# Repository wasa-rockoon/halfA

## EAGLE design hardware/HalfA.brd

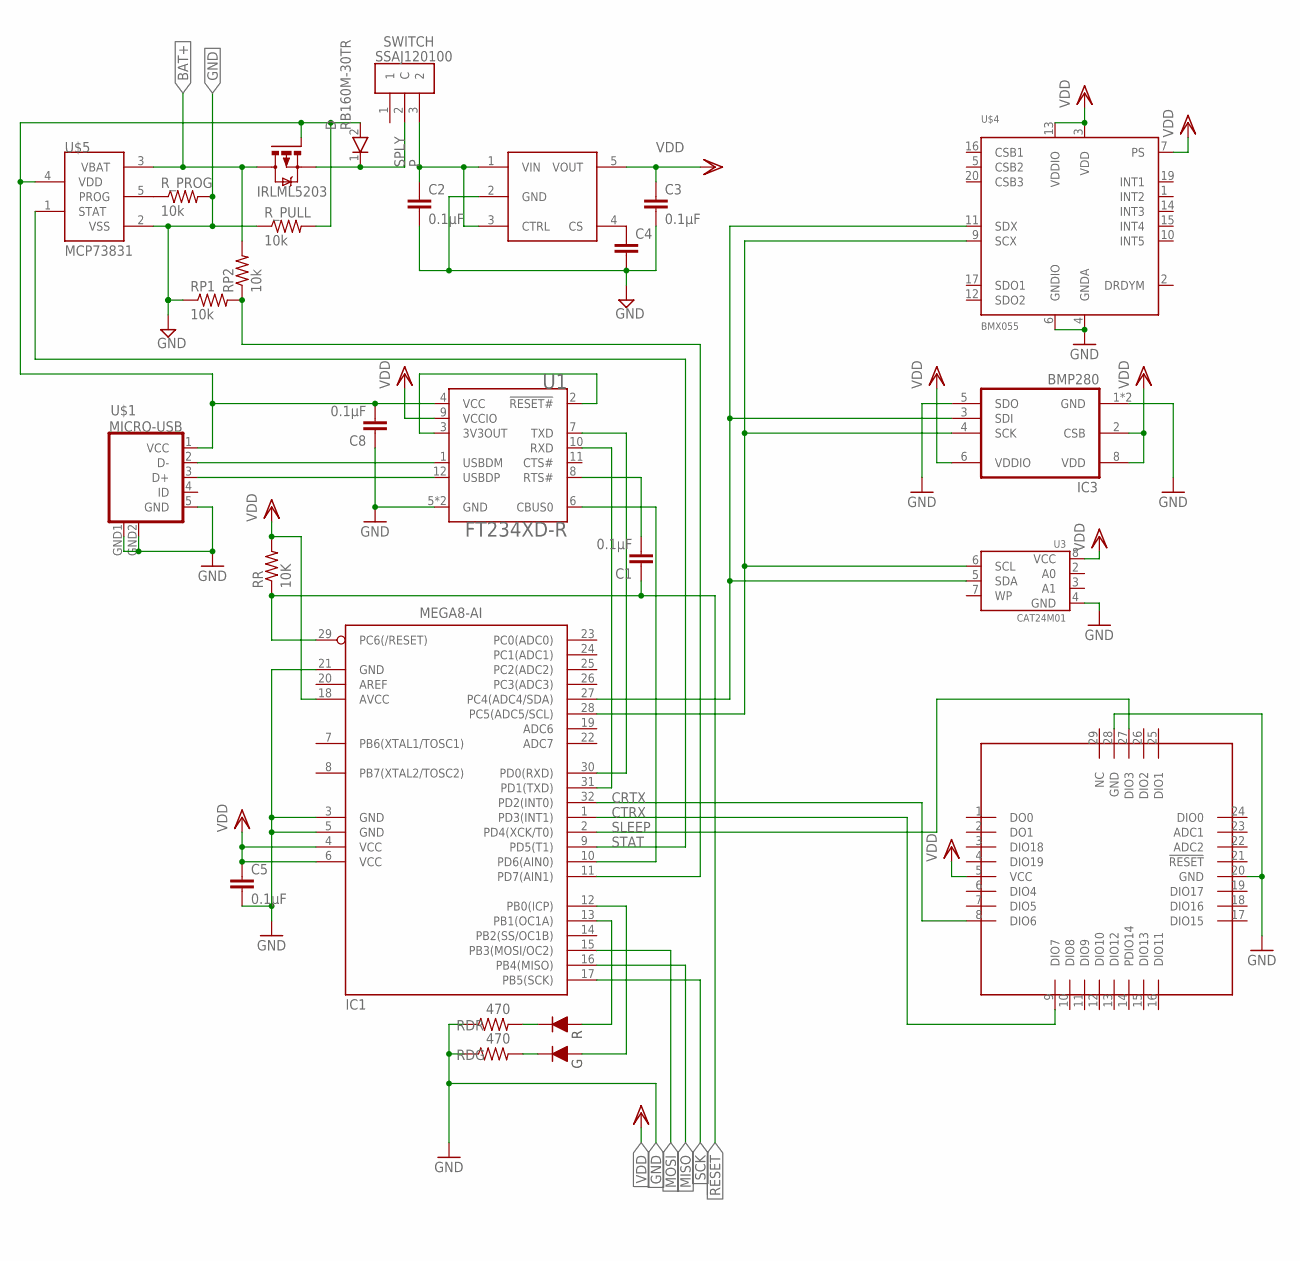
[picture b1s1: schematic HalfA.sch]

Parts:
C1, C2, C3, C5, C8: 0.1µF; C0402K
C4: C-EUC0402K; C0402K
D: RB160M-30TR; SODFL3516X90N
IC1: MEGA8-AI; TQFP32-08
IC3: BMP280
Q1: IRLML5203; MICRO3
RDG: 470; R0402
RDR: 470; R0402
RP1, RP2: 10k; R0402
RR: 10K; R0402
R_PROG: 10k; R0402
R_PULL: 10k; R0402
SWITCH: SSAJ120100
U1: FT234XD-R; SON45P300X300X80-13N
U3: CAT24M01; SO-8
U$1: MICRO-USB
U$2: NJM12888F
U$3: LITE
U$4: BMX055
U$5: MCP73831; SOT23-5L
U$6: SML-P24MUW

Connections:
3.3V: U1.2 (!RESET#), U1.3 (3V3OUT)
5V: C8.2, D.2 (A), Q1.1 (G), R_PULL.2, U1.4 (VCC), U$1.1 (VCC), U$5.4 (VDD)
!RESET!: C1.1, IC1.29 (PC6(/RESET)), RR.1
!RTS!: C1.2, U1.8 (RTS#)
BAT: IC1.11 (PD7(AIN1)), RP1.2, RP2.1
BAT+: Q1.3 (D), RP2.2, U$5.3 (VBAT)
CRTX: IC1.32 (PD2(INT0)), U$3.8 (DIO6)
CS: C4.1, U$2.4 (CS)
CTRX: IC1.1 (PD3(INT1)), U$3.9 (DIO7)
D+: U1.12 (USBDP), U$1.3 (D+)
D-: U1.1 (USBDM), U$1.2 (D-)
GND: C2.2, C3.2, C4.2, C5.2, C8.1, IC1.3 (GND), IC1.5 (GND), IC1.21 (GND), IC3.1 (GND), IC3.5 (SDO), IC3.7 (GND), RDG.1, RDR.1, RP1.1, R_PROG.2, R_PULL.1, U1.5 (GND), U1.13 (GND), U3.4 (GND), U$1.5 (GND), U$1.GND1 (GND), U$1.GND2 (GND), U$2.2 (GND), U$3.20 (GND), U$3.28 (GND), U$4.4 (GNDA), U$4.6 (GNDIO), U$5.2 (VSS)
LED: IC1.13 (PB1(OC1A)), U$6.2 (RA)
LEDG: IC1.12 (PB0(ICP)), U$6.1 (GA)
MISO: IC1.16 (PB4(MISO))
MOSI: IC1.15 (PB3(MOSI/OC2))
unnamed: RDR.2, U$6.3 (RC)
unnamed: RDG.2, U$6.4 (GC)
unnamed: R_PROG.1, U$5.5 (PROG)
P: C2.1, SWITCH.3 (2), U$2.1 (VIN), U$2.3 (CTRL)
SCK: IC1.17 (PB5(SCK))
SCL: IC1.28 (PC5(ADC5/SCL)), IC3.4 (SCK), U3.6 (SCL), U$4.9 (SCX)
SDA: IC1.27 (PC4(ADC4/SDA)), IC3.3 (SDI), U3.5 (SDA), U$4.11 (SDX)
SLEEP: IC1.2 (PD4(XCK/T0)), U$3.27 (DIO3)
SPLY: D.1 (K), Q1.2 (S), SWITCH.2 (C)
STAT: IC1.9 (PD5(T1)), U$5.1 (STAT)
TX/RX: IC1.10 (PD6(AIN0)), U1.6 (CBUS0)
URTX: IC1.30 (PD0(RXD)), U1.7 (TXD)
UTRX: IC1.31 (PD1(TXD)), U1.10 (RXD)
VDD: C3.1, C5.1, IC1.4 (VCC), IC1.6 (VCC), IC1.18 (AVCC), IC3.2 (CSB), IC3.6 (VDDIO), IC3.8 (VDD), RR.2, U1.9 (VCCIO), U3.8 (VCC), U$2.5 (VOUT), U$3.5 (VCC), U$4.3 (VDD), U$4.7 (PS), U$4.13 (VDDIO)

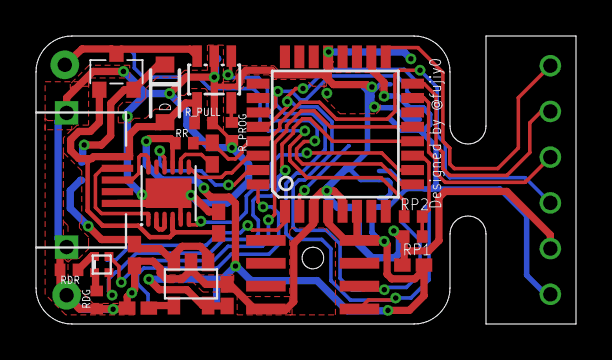
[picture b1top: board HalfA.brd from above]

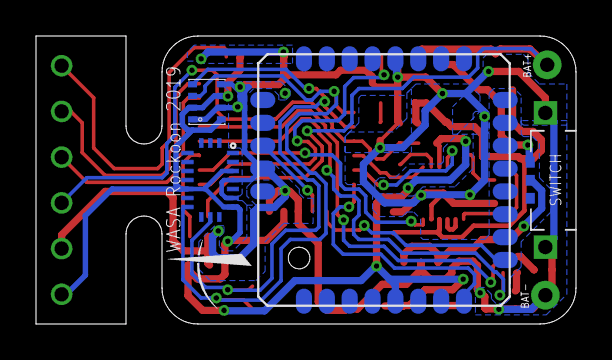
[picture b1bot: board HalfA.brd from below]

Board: 2 copper layers, 30.0 x 16.0 mm, 26 parts (4 on the bottom side), 27 nets.

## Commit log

2019-10-18 Eagle project setting
2021-06-23 Add some software
2022-04-30 Update firmware
2022-05-11 Check BMP280
